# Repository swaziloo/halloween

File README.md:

# Hallowe'en Projects #

___
## [Animatronic Crow](animatronicCrow/README.md) ##

A 3D printable crow model that turns its head, blinks LED eyes, moves its beak and squawks when it sees your friends or trick-or-treaters.

___
## [Creature Control PCB](creatureControl/README.md) ##

A PCB to make building animated projects easier to put together.

___
### [Our Hallowe'en Decoration Gallery](https://www.monkeymind.com/halloween) ###

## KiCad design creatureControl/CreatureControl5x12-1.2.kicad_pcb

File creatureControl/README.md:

# Creature Control PCB #
When hand soldering a board to enable the animatronic crow I realized that I wanted a half-dozen crows and maybe some talking skulls and hand soldering wasn't my favorite way to spend my time.
Hence Creature Control 5x12. Designed to enable a bunch of capability using an inexpensive and easy to program Raspberry Pi 2040 in the tiny Waveshare Zero format.

*I likely have extra PCBs&mdash;contact me directly if interested in PCB(s) at cost.*

## 5x12 v1.0 ##
Provides a 5-volt 3-amp power rail to supply 3 servos and 2 steppers controlled by a RP2040-Zero which is also wired to incorporate 2 LEDs, 2 motion sensors, the DFPlayer Mini mp3 player and a pin header for the remaining pins.
Designed to be hand-soldered and easily programmable using Arduino libraries.
### v1.1 2025-09 ###
Larger PTH (0.9mm) for MCU and mp3 player mounts, 
add 1KΩ serial resistor for DFPlayer RX (MCU GP0) connection, 
add capacitor (104) for DFPlayer 3V3, 
remove incorrect silk for C7 and C8 value,
rotate sensor mounts for better routing,
update schema.
### v1.2 2025-10 ###
Move DFPlayer Mini to 5V supply and add additional bulk/filtering capacitors (1µF, 220µF),
add filtering capacitor (0.1µF) at 5V power supply,
move servos 1-3 to GP27-GP29,
move GP2-GP4 to expansion header,
rotate DFPlayer Mini,
(re)arrange silks,
update schema.

*Gerber files have been produced for JLCPCB but may work elsewhere.*

### VITAL IMPORTANT SAFETY NOTICE! ###
*The 5 volt power rail allows for multiple source connections but only one should be used at any given time.* 
*Do not connect more than one 5 volt source to the power rail!*
(Unless you really know what you're doing.)
It is safe to connect the power to the 5v rail and the RP2040-Zero to your PC at the same time&mdash;in fact it's necessary for testing.
### Parts List ###
The intent is that one would install only the components needed for a project.

| Qty            | Ref        | Part                                                         | Note                                                                                                     |
|----------------|------------|--------------------------------------------------------------|----------------------------------------------------------------------------------------------------------|
| 1              |            | RP2040-Zero                                                  | Waveshare or equivalent.                                                                                 |
| 1              | D2         | 1N5819 Schottky Diode                                        | For RP2040-Zero VCC.                                                                                     |
| 1              |            | DFPlayer Mini                                                | DFRobot or equivalent.                                                                                   |
| 3-4            | C7-C9, C12 | 100nF 50v Ceramic Capacitor (104)                            | (v1.1+) for DFPlayer Mini 5V, (v1.2) input 5V, ULN2003A.                                                 |
| 1              | C10        | 1µF 50v Ceramic Capacitor (105)                              | (v1.2) For DFPlayer Mini midrange filter.                                                                |
| 1              | C11        | 220µF 10-16v Electrolytic Capacitor                          | (v1.2) For DFPlayer Mini .                                                                               |
| 1              | R6         | 1KΩ Resistor                                                 | (v1.1+) for MCU GP0->DFPlayer Mini RX                                                                    |
| 1-2            |            | ULN2003A                                                     | Stepper driver.                                                                                          |
| 1-2 (optional) |            | IC DIP Socket 16-Pin                                         | For ULN2003A. Or just solder directly to the board.                                                      |
| 1-2            |            | XH2.54mm 5-Pin Connector                                     | Straight pin for stepper.                                                                                |
| 1 (optional)   | D1         | 3mm LED                                                      | For power rail indicator.                                                                                |
| 1 (optional)   | R3         | Resistor for power indicator LED                             | I used 2.2kΩ for a blue 3mm LED.                                                                         |
| 1-2            | R4,R5      | Resistor for external LEDs                                   | Based on LED(s) to be used.                                                                              |
| 1-5            | C2-C6      | 100µF 10-16v Electrolytic Capacitor                          | One for each 5v servo and stepper.                                                                       |
| 1              | C1         | 1000µF 10-16v Electrolytic Capacitor                         | For 5v rail.                                                                                             |
| 1 (optional)   | J2         | 5.5x2.1MM DC-005 Power Jack                                  | If using a 5v/3A adapter.                                                                                |
| 1 (optional)   | J1         | USB-C 6-pin Surface Mount                                    | If using a USB battery.                                                                                  |
| 2 (optional)   | R1,R2      | 5.1kΩ Resistors                                              | If using a USB battery.                                                                                  |
| 1 (optional)   | J3         | KF350-2P 3.5mm Pitch 2Pin PCB Screw Terminal Block Connector | If using a wired 5v source or drain. Also useful if needing to share ground with an external power rail. |
| optional       |            | 2.54mm Pin Headers                                           | For board connections.                                                                                   |

## Building the CC5x12 ##

* You do not need to fill the board. It is perfectly acceptable to install only the connections and components you intend to use.
* If you are installing the USB-C socket, do that first and test the electrical connections. Every other component is easier to hand solder.
* The RP2040-Zero can be powered by its USB-C connection or the board 5v power, but it will not provide power to the steppers, servos, or DFPlayer (since v1.2). LEDs and sensors draw power from the RP2040-Zero 3V3.
* The C1 capacitor is intended to smooth out the 5v supply for the board. C2-C6 & C11 provide demand power for their nearby stepper, servo, or DFPlayer Mini. Only install these caps for the components you intend to connect.
___

## Testing ##
Install the Arduino IDE and the following libraries:
[AccelStepper](https://www.airspayce.com/mikem/arduino/AccelStepper),
[DFRobotDFPlayerMini](https://github.com/DFRobot/DFRobotDFPlayerMini),
[arduino-pico](https://github.com/earlephilhower/arduino-pico) by Earle Philhower,
[Adafruit NeoPixel](https://github.com/adafruit/Adafruit_NeoPixel).
Install using the library manager in the Arduino IDE.

* Enable the *Waveshare RP2040-Zero* board in the board manager.
* Connect power to one of the 5v inputs and the RP2040-Zero to your pc. 
* Select the connected device/port and ensure the Waveshare RP2040-Zero board is assigned.
* Open the [BoardTest](BoardTest) sketch with the Arduino IDE.
* Set 'true' for available components at the top of the sketch. 
* Select the 'Upload' button.
* The sketch should compile, the board should initialize, and a test loop should run.

The steppers, servos, and MP3 components will cycle.
The LED(s) will reflect the sensor(s) states.

___
## Notes and Issues: ##

### Volume Issues v1.0 and v1.1 ###
The DFPlayer Mini is being powered off the RP2040-Zero 3V3 on these boards which doesn't provide enough power to handle max draw at high volume.
The fix for these boards is to pull the VCC pin from the header and wire to a nearby 5V connection.
Add a 220µF electrolytic and a 1µF (105) ceramic at the power tap and pull a twisted pair of 5V/GND to the DFPlayer, connecting a 0.1µF (104) between ground and VCC at the connection point.
The easier fix is to lower the volume to one that the MCU will support. 
Around 22-25/30.
TX/RX are already shifted to 3.3V for compatibility with MCU communication.

### Connecting to a 12v Rail ###
You should be able to control 12v steppers and servos using the CC5X12 by eliminating the 5v connection to them and providing separate power. 
If you do this, you will want to pull a shared ground over from the block connector or another board source.
*I have not tested this functionality.*

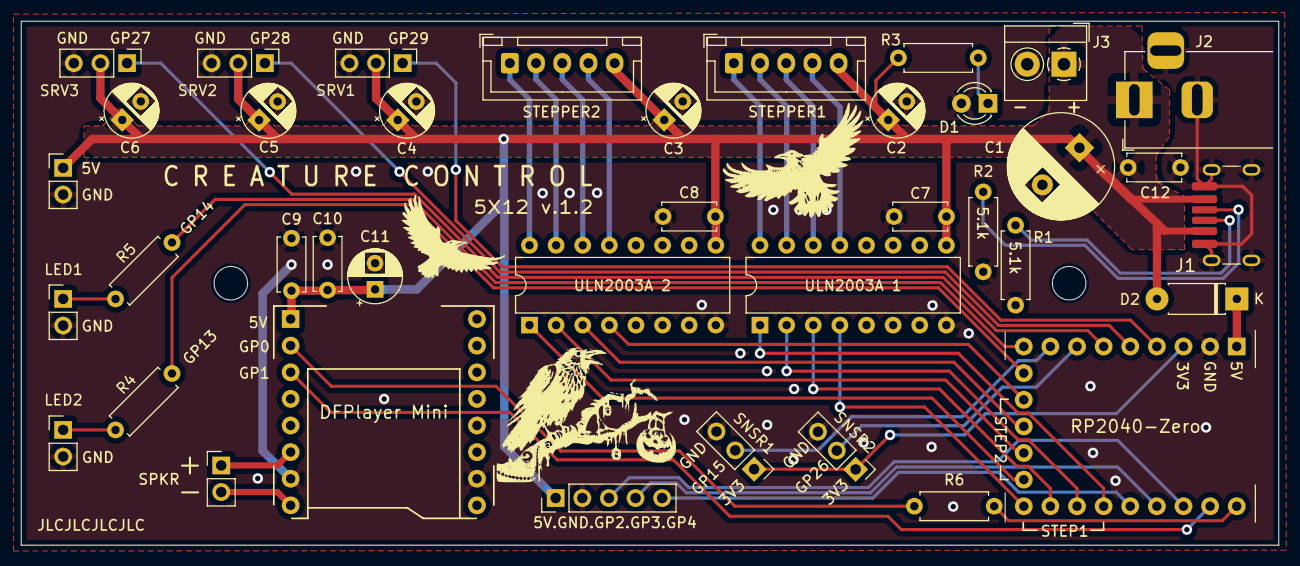
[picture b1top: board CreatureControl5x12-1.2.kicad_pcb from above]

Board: 2 copper layers, 120.0 x 50.0 mm, 38 parts (0 on the bottom side), 37 nets.

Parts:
5V: PinHeader_1x02_P2.54mm_Vertical
 R5: 2.2 kΩ; R_Axial_DIN0207_L6.3mm_D2.5mm_P7.62mm_Horizontal
C1: CP_Radial_D10.0mm_P5.00mm
C2, C3, C4, C5, C6, C11: CP_Radial_D5.0mm_P2.50mm
C7, C8: 10nf; C_Disc_D5.0mm_W2.5mm_P5.00mm
C9, C10, C12: C_Disc_D5.0mm_W2.5mm_P5.00mm
D1: LED_D3.0mm
D2: D_DO-41_SOD81_P7.62mm_Horizontal
DFPlayer Mini: DFPlayer Mini
J1: USB_C_Receptacle_GCT_USB4125-xx-x-0190_6P_TopMnt_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; USB_C_Receptacle_GCT_USB4125-xx-x-0190_6P_TopMnt_Horizontal
J2: BarrelJack_Horizontal
J3: TerminalBlock_4Ucon_1x02_P3.50mm_Horizontal
LED1, LED2: PinHeader_1x02_P2.54mm_Vertical
R1, R2, R6: 5.1 kΩ; R_Axial_DIN0207_L6.3mm_D2.5mm_P7.62mm_Horizontal
R3, R4: 2.2 kΩ; R_Axial_DIN0207_L6.3mm_D2.5mm_P7.62mm_Horizontal
RP2040-Zero: RP2040 Zero
SNSR1, SNSR2: PinHeader_1x03_P2.54mm_Vertical
SPKR: PinHeader_1x02_P2.54mm_Vertical
SRV1, SRV2, SRV3: PinHeader_1x03_P2.54mm_Vertical
STEPPER1, STEPPER2: JST_XH_B5B-XH-A_1x05_P2.50mm_Vertical
ULN2003A 1, ULN2003A 2: DIP-16_W7.62mm

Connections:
3V3: RP2040-Zero.3, SNSR1.1, SNSR2.1
5V: 5V.1, C1.1, C2.1, C3.1, C4.1, C5.1, C6.1, C7.1, C8.1, C9.1, C10.1, C11.1, C12.1, D2.2, DFPlayer Mini.1, J1.A9, J1.B9, J2.1, J3.1, R3.1, SRV1.2, SRV2.2, SRV3.2, STEPPER1.5, STEPPER2.5, ULN2003A 1.9, ULN2003A 2.9
A5: J1.A5, R1.2
B5: J1.B5, R2.2
D1: D1.1, R3.2
DFRX: DFPlayer Mini.2, R6.2
GND: 5V.2, C1.2, C2.2, C3.2, C4.2, C5.2, C6.2, C7.2, C8.2, C9.2, C10.2, C11.2, C12.2, D1.2, DFPlayer Mini.7, DFPlayer Mini.15, J1.A12, J1.B12, J1.S1, J2.2, J2.3, J3.2, LED1.2, LED2.2, R1.1, R2.1, RP2040-Zero.2, SNSR1.3, SNSR2.3, SRV1.3, SRV2.3, SRV3.3, ULN2003A 1.8, ULN2003A 2.8
GP0: R6.1, RP2040-Zero.10
GP1: DFPlayer Mini.3, RP2040-Zero.11
GP5: RP2040-Zero.15, ULN2003A 1.1
GP6: RP2040-Zero.16, ULN2003A 1.2
GP7: RP2040-Zero.17, ULN2003A 1.3
GP8: RP2040-Zero.18, ULN2003A 1.4
GP9: RP2040-Zero.23, ULN2003A 2.1
GP10: RP2040-Zero.22, ULN2003A 2.2
GP11: RP2040-Zero.21, ULN2003A 2.3
GP12: RP2040-Zero.20, ULN2003A 2.4
GP13: R4.2, RP2040-Zero.19
GP14: R5.2, RP2040-Zero.9
GP15: RP2040-Zero.8, SNSR1.2
GP26: RP2040-Zero.7, SNSR2.2
GP27: RP2040-Zero.6, SRV3.1
GP28: RP2040-Zero.5, SRV2.1
GP29: RP2040-Zero.4, SRV1.1
LED1: R5.1, LED1.1
LED2: LED2.1, R4.1
RP-5V: D2.1, RP2040-Zero.1
S1-1: STEPPER1.1, ULN2003A 1.16
S1-2: STEPPER1.2, ULN2003A 1.15
S1-3: STEPPER1.3, ULN2003A 1.14
S1-4: STEPPER1.4, ULN2003A 1.13
S2-1: STEPPER2.1, ULN2003A 2.16
S2-2: STEPPER2.2, ULN2003A 2.15
S2-3: STEPPER2.3, ULN2003A 2.14
S2-4: STEPPER2.4, ULN2003A 2.13
SPKR+: DFPlayer Mini.6, SPKR.1
SPKR-: DFPlayer Mini.8, SPKR.2

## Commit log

2025-08-29 Initial repository with crow additions
2025-08-29 mostly empty readme
2025-08-29 add images
2025-09-09 Initial remix files and build guide
2025-09-09 Small corrections
2025-09-09 Adding Creature Control 5x12 PCB files
2025-09-09 Removing temporary files.
2025-09-09 Added link to CC plus small edits.
2025-09-09 Minor clarifications
2025-09-19 Add banner image
2025-09-22 Remove old schematic--rename new one
2025-09-22 Update stepper mount and head support interface
2025-09-24 Update build guide for crow head with latest changes
2025-09-28 Body models and Head modifications
2025-09-28 Adding PIR window cutout template
2025-09-28 Fix non-manifold body edges, add print instructions & images
2025-09-28 Fix unclear text
2025-09-29 Fix typo
2025-09-29 Update info and instructions
2025-10-06 update beak, add actuator, update build
2025-10-06 fix copy-paste error
2025-10-06 Add test script for CC5x12
2025-10-08 Add software and sounds
2025-10-08 Update updates in README
2025-10-08 Update sensor mounts and add PIR hole plug
2025-10-08 Disable test mode for default
2025-10-08 Adjust defaults
2025-10-08 Extra PCBs in hand
2025-10-09 Updated and clarified Software instructions
2025-10-10 Tiny clarification
2025-10-10 Clarify version for parts list
2025-10-10 Upgrade bottoms silkscreen art
2025-10-10 Clarify some build instructions
2025-10-11 Add explicit PWM settings for SG90 servo
2025-10-12 Add optional NeoPixel, v1.1 bodge, scold rotate
2025-10-12 Fixed typo
2025-10-13 Refine PIR behavior, prevent scolds from lining up too close to squawks
2025-10-13 Add/rename simple max volume modification
2025-10-15 Update to CC5x12 1.2 image
2025-10-15 Include no-sensor mode. Refine interactions.
2025-10-21 Update software config re: sensor mode options
2025-10-21 Better balance PCB mount position and enlarge insert melt holes
2025-10-21 Add LD1020 radar installation instructions
2025-10-23 Fix newline
2025-10-23 Adding board images
2025-10-23 minor edits
2025-10-28 Adding link to German translation
2025-12-18 Update default servo pin and some build instructions
2026-01-02 Add SENSOR_MODE_BUTTON for "Try Me" interaction
2026-01-02 Model updates to speaker, magnets, drainage, feet, inserts, PIR/fresnel
2026-01-02 Remove magnet shims
2026-01-03 Update guides to match latest files
2026-01-13 Add 8006 fresnel lens clarification
2026-01-22 Restoring feet without side hole (thanks padpumpkin)
2026-01-23 Clarify beak servo adjustment strategy
2026-01-25 Longer speaker ring screw needed
2026-02-02 Crow control improved and expanded
2026-02-02 Fix small issues, clarify, tidy up formatting
2026-02-04 Incorporate initial (static) ESP32-S3-Zero control software
2026-02-05 Safer PWM limits
2026-02-06 Fix missing last-but-one frame bug, lighten PROGMEM lookups when animation is unchanged
2026-02-08 Better range handling and update build guide software steps
2026-02-08 Clarify player start delay and direct to Software section where appropriate
2026-02-08 Update YouTube video link with calibration instructions
2026-02-09 Adding short delay for DFPlayer start/index
